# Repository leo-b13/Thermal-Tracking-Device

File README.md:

# Thermal Tracking Device #
* This code uses an ESP32 mini, a Panasonic Grid-EYE sensor, SG90 micro servo motors, and several electrical components in order to direct air towards a person

* Tracking Device Processing is code to be used in the Processing Application to display the data from the GridEYE
  * This requires serial data so data must be printed in the serial monitor each loop
  * Sometimes the processing code will not upload due to a NaN error. Just keep trying to upload it (maybe 3-5 times) and it should upload succesfully

* Epsilon is the main version. This was designed to work with an ESP32 mini microcontroller. The pinout is seen below.

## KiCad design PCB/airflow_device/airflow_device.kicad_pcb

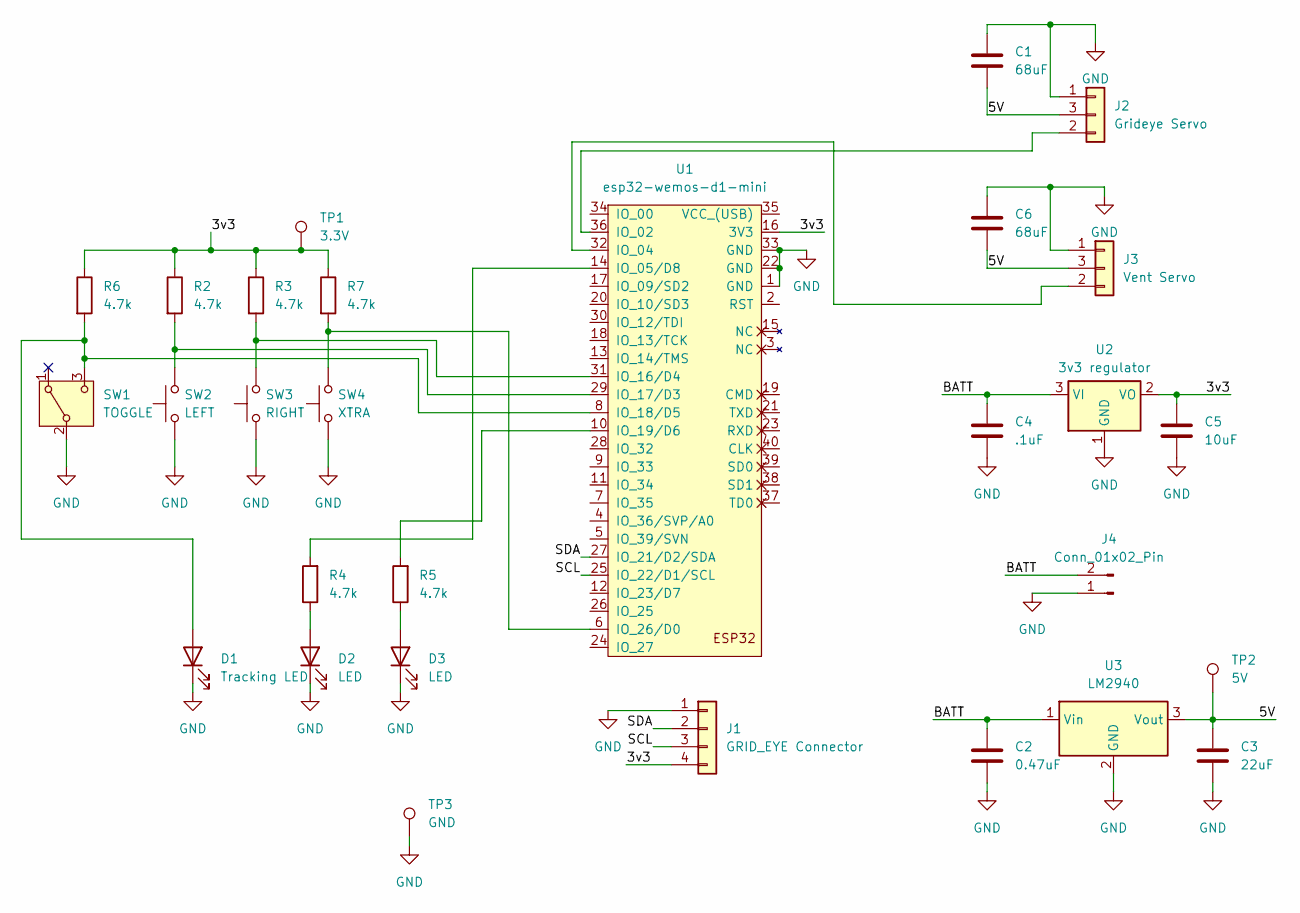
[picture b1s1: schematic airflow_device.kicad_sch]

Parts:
C1, C6: 68uF; CP_Radial_D7.5mm_P2.50mm
C2: 0.47uF; C_0805_2012Metric_Pad1.18x1.45mm_HandSolder
C3: 22uF; C_0805_2012Metric_Pad1.18x1.45mm_HandSolder
C4: .1uF; C_0805_2012Metric_Pad1.18x1.45mm_HandSolder
C5: 10uF; C_0805_2012Metric_Pad1.18x1.45mm_HandSolder
D1: Tracking LED; LED_D3.0mm
D2, D3: LED; LED_D3.0mm
J1: GRID_EYE Connector; PinHeader_1x04_P2.54mm_Vertical
J2: Grideye Servo; PinHeader_1x03_P2.54mm_Vertical
J3: Vent Servo; PinHeader_1x03_P2.54mm_Vertical
J4: Conn_01x02_Pin; PinSocket_1x02_P2.54mm_Vertical
R2, R3, R4, R5, R6, R7: 4.7k; R_0805_2012Metric_Pad1.20x1.40mm_HandSolder
SW1: TOGGLE; PinHeader_1x03_P2.54mm_Vertical
SW2: LEFT; SW_PUSH_6mm_H5mm
SW3: RIGHT; SW_PUSH_6mm_H5mm
SW4: XTRA; SW_PUSH_6mm_H5mm
TP1: 3.3V; TestPoint_Pad_2.5x2.5mm
TP2: 5V; TestPoint_Pad_2.5x2.5mm
TP3: GND; TestPoint_Pad_2.5x2.5mm
U1: esp32-wemos-d1-mini
U2: 3v3 regulator; TO-220-3_Vertical
U3: LM2940; TO-220-3_Vertical

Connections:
/3v3: C5.1, J1.4 (Vin), R2.1, R3.1, R6.1, R7.1, TP1.1, U1.16 (3V3), U2.2 (VO)
/5V: C1.2, C3.1, C6.2, J2.3 (Vin), J3.3 (Vin), TP2.1, U3.3 (Vout)
/BATT: C2.1, C4.1, J4.2 (BATT), U2.3 (VI), U3.1 (Vin)
/SCL: J1.3 (SCL), U1.25 (IO_22/D1/SCL)
/SDA: J1.2 (SDA), U1.27 (IO_21/D2/SDA)
GND: C1.1, C2.2, C3.2, C4.2, C5.2, C6.1, D1.1 (K), D2.1 (K), D3.1 (K), J1.1 (GND), J2.1 (GND), J3.1 (GND), J4.1 (GND), SW1.2 (B), SW2.1, SW3.1, SW4.1, TP3.1, U1.1 (GND), U1.22 (GND), U1.33 (GND), U2.1 (GND), U3.2 (GND)
unnamed: D1.2 (A), R6.2, SW1.3 (C), U1.8 (IO_18/D5)
unnamed: D2.2 (A), R4.1
unnamed: D3.2 (A), R5.1
unnamed: J2.2 (SIG), U1.36 (IO_02)
unnamed: J3.2 (SIG), U1.32 (IO_04)
unnamed: R4.2, U1.14 (IO_05/D8)
unnamed: R3.2, SW3.2, U1.31 (IO_16/D4)
unnamed: R2.2, SW2.2, U1.29 (IO_17/D3)
unnamed: R5.2, U1.10 (IO_19/D6)
unnamed: R7.2, SW4.2, U1.6 (IO_26/D0)

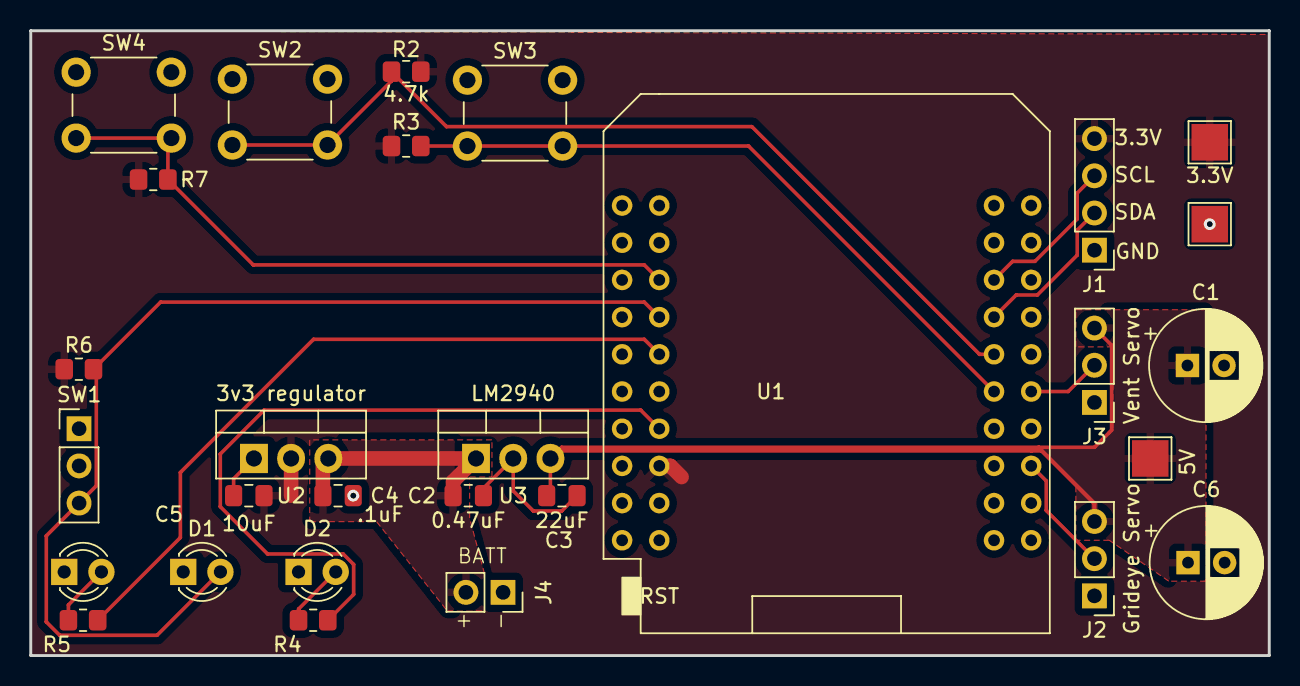
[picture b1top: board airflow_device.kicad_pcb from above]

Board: 2 copper layers, 84.6 x 42.7 mm, 29 parts (0 on the bottom side), 16 nets.

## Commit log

2024-11-05 Added basic tracking code
2024-11-07 Updated delta tracking code
    -Added debug functions
    -Added minTemp calculation
2024-11-09 Epsilon: Delta tracking + integration
    Integration includes button and servo testing
2024-11-09 Began to add mode toggle
2024-11-09 Added servo pos stuff
2024-11-10 Grideye function added
2024-11-13 Initial Commit for PCB
    Included are footprints and symbols for the components that I had to make custom.
2024-11-13 Adding more components
2024-11-13 WIP Searching, General Adjustment
    -added wip searching function
    -messed with some functions, got rid of some and modified some
    -got rid of Y vent / motor stuff since we won't be using it
    -moved some stuff around in general
2024-11-14 Adding more components, and fixing footprints
2024-11-14 Fixed pin assignment, for testing
2024-11-15 Deleted zeta
2024-11-16 Adding more footprints
2024-11-18 Likely Functional PCB
2024-11-19 Created files folder
2024-11-19 WIP SEARCHING MODE
2024-11-19 Rename gridEYE_bb_final.ino to WIP_SEARCH.ino
2024-11-19 Added 68uF caps for servos
2024-11-20 Fixed servo current draw
    -Fixed servo current draw (changed PWM settings)
2024-11-20 Fixed formatting
2024-11-20 PCB Done
2024-11-20 literally nothing
2024-11-27 WIP PID testing added
2024-11-29 Proportional Gain Only, 64 pixel scan
2024-12-02 Updated for PCB + Processing
2024-12-03 Added processing code file
2024-12-06 Added vent servo motor + upped proportional a bit
2024-12-06 Flipped vertically
